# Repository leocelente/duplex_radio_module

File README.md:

# Duplex SX126x Radio Module

Board with 2 radios, STM32 and USB or CAN

## Schematic

## Layout

## Notes
The STM32F103 can't it isn't possible to use both CAN and USB 
([Source](https://community.st.com/s/article/FAQ-Concurrent-use-of-USB-and-CAN-with-STM32F103))

The intended use is to switch the interface based on the state of the SEL pin during startup process. 

## Manufacture and Assembly
The generic components and the microcontroller were chosen based on JLCPCB's Basic Parts library. That includes only the STM32, CAN transceiver, LEDs, resistors, capacitors and crystals. All connectors and the main radio modules are not included. 

|                   |           |
|-------------------|-----------|
| PCB Manufacture   | $7.00     |
| PCB Assembly      | $27.62    |
| Shipping          | $10.17    |
| Total             | $44.79    |

For 5 boards. 

Since the conversion rate of USD to BRL is around R$5,00 the cost would be R$45,00 per board. Take note that the radio module costs around R$20 on aliexpress without shipping.

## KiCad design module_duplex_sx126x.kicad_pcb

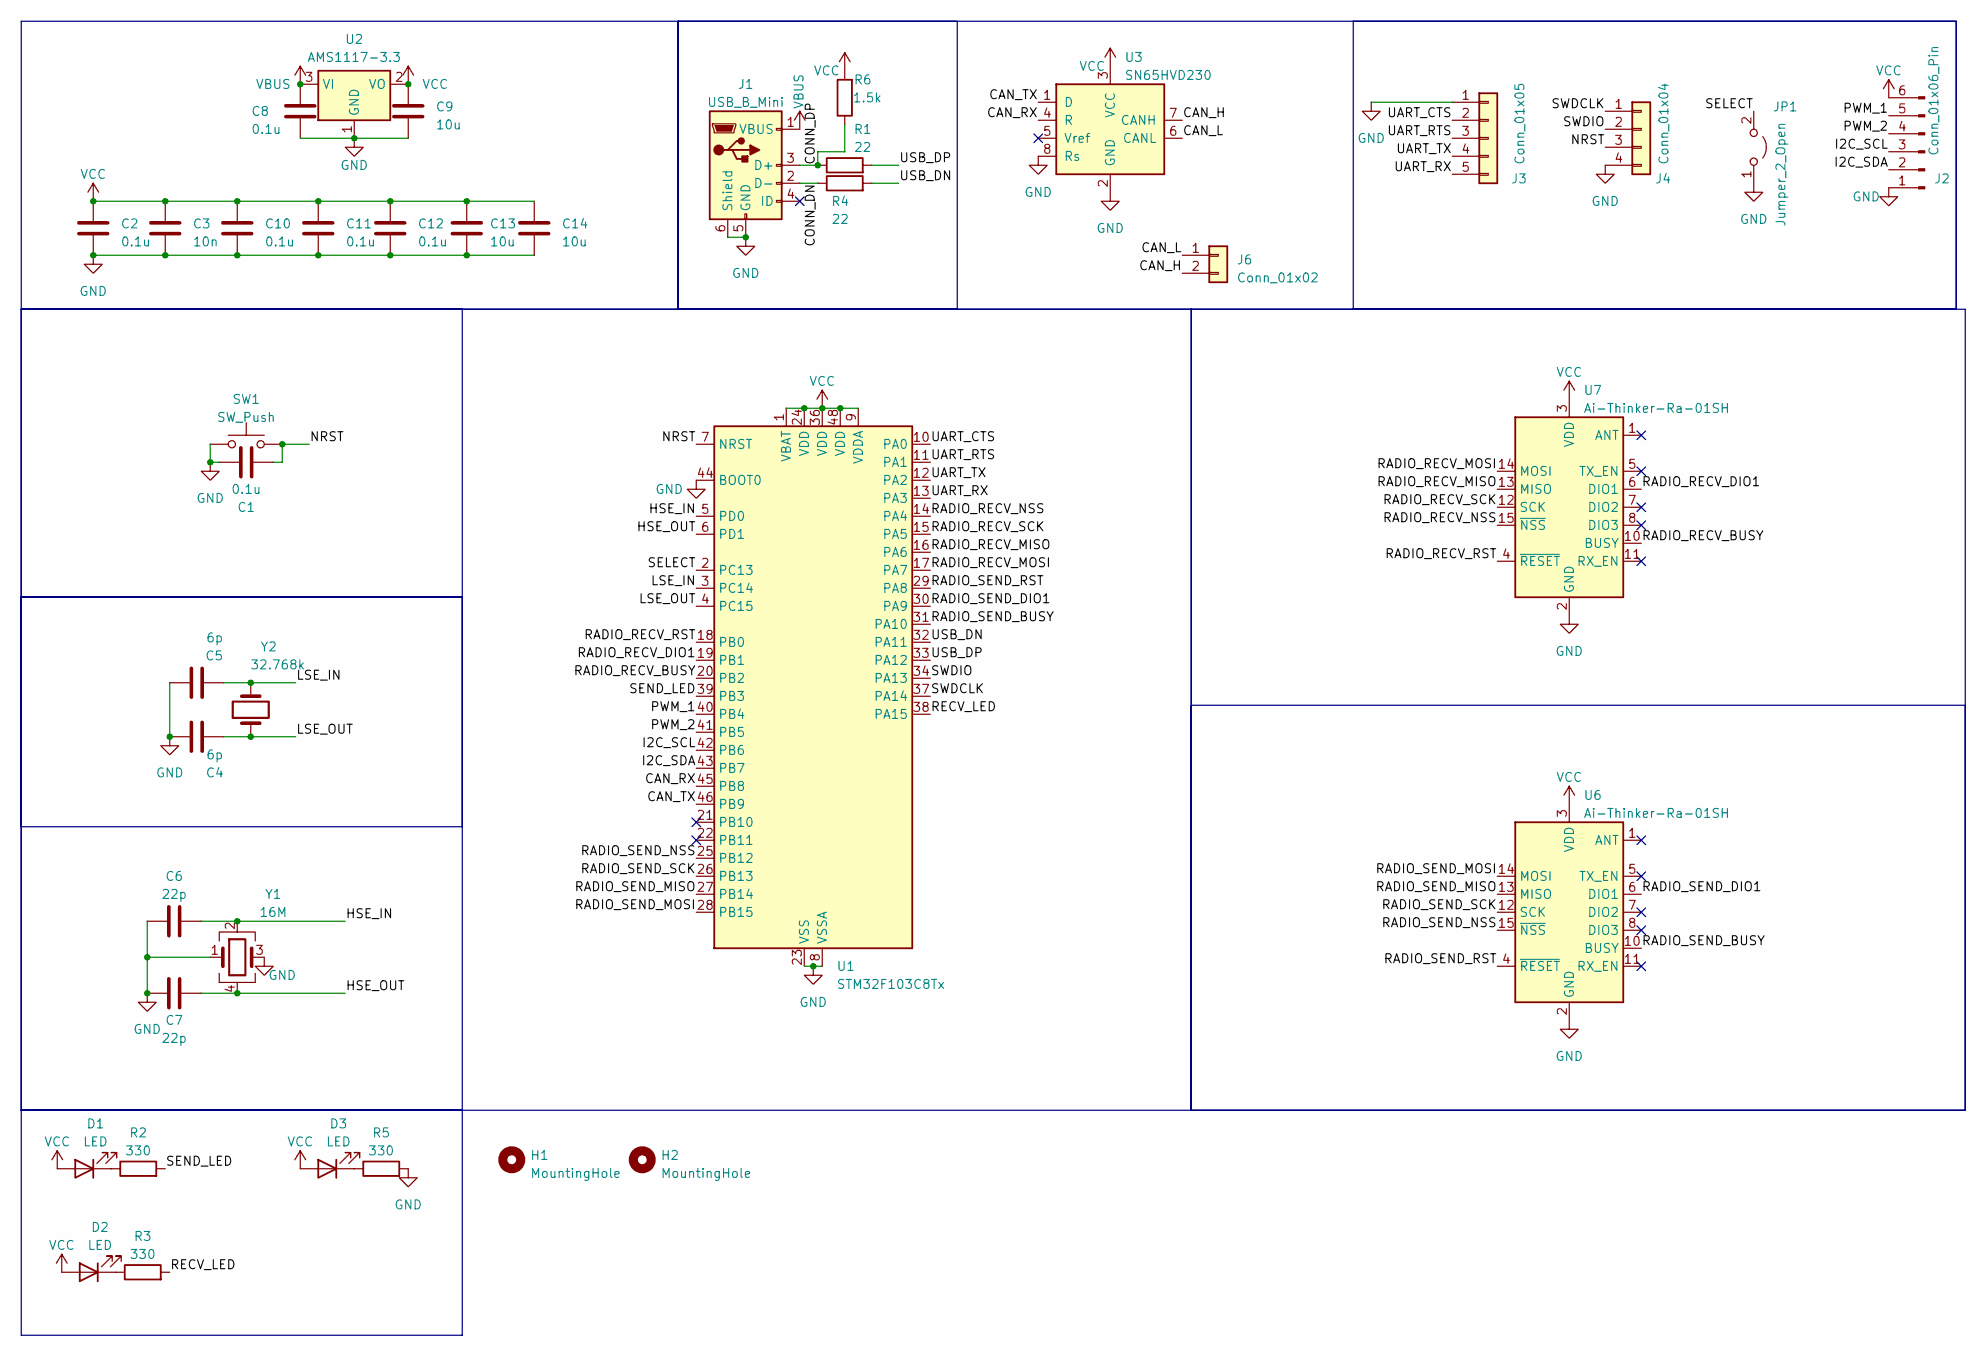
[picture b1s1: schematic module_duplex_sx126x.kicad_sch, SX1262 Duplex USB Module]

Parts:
C1, C2, C8, C10, C11, C12: 0.1u; C_0603_1608Metric; LCSC C14663
C3: 10n; C_0603_1608Metric; LCSC C57112
C4, C5: 6p; C_0603_1608Metric; LCSC C37474
C6, C7: 22p; C_0603_1608Metric; LCSC C1653
C9, C13, C14: 10u; C_0805_2012Metric; LCSC C19702
D1: LED; LED_0603_1608Metric; LCSC C72043
D2: LED; LED_0603_1608Metric; LCSC C72041
D3: LED; LED_0603_1608Metric; LCSC C2286
H1, H2: MountingHole; MountingHole_3.2mm_M3_Pad
J1: USB_B_Mini; USB_Mini-B_Lumberg_2486_01_Horizontal
J2: Conn_01x06_Pin; PinHeader_1x06_P2.54mm_Vertical
J3: Conn_01x05; JST_PH_S5B-PH-K_1x05_P2.00mm_Horizontal
J4: Conn_01x04; JST_PH_B4B-PH-K_1x04_P2.00mm_Vertical
J6: Conn_01x02; JST_PH_S2B-PH-K_1x02_P2.00mm_Horizontal
JP1: Jumper_2_Open; PinHeader_1x02_P2.54mm_Vertical
R1, R4: 22; R_0603_1608Metric; LCSC C23345
R2, R3, R5: 330; R_0603_1608Metric; LCSC C23138
R6: 1.5k; R_0603_1608Metric; LCSC C22843
SW1: SW_Push; SW_SPST_TL3342; LCSC C318884
U1: STM32F103C8Tx; LQFP-48_7x7mm_P0.5mm; LCSC C8734
U2: AMS1117-3.3; SOT-223-3_TabPin2; LCSC C6186
U3: SN65HVD230; SOIC-8_3.9x4.9mm_P1.27mm; LCSC C12084
U6, U7: Ai-Thinker-Ra-01SH; Ai-Thinker-Ra-01-LoRa
Y1: 16M; Crystal_SMD_3225-4Pin_3.2x2.5mm; LCSC C13738
Y2: 32.768k; Crystal_SMD_3215-2Pin_3.2x1.5mm; LCSC C32346

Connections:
/CAN_H: J6.2, U3.7 (CANH)
/CAN_L: J6.1, U3.6 (CANL)
/CAN_RX: U1.45 (PB8), U3.4 (R)
/CAN_TX: U1.46 (PB9), U3.1 (D)
/CONN_DN: J1.2 (D-), R4.1
/CONN_DP: J1.3 (D+), R1.1, R6.1
/HSE_IN: C6.2, U1.5 (PD0), Y1.2
/HSE_OUT: C7.2, U1.6 (PD1), Y1.4
/I2C_SCL: J2.3, U1.42 (PB6)
/I2C_SDA: J2.2, U1.43 (PB7)
/LSE_IN: C5.2, U1.3 (PC14), Y2.2
/LSE_OUT: C4.2, U1.4 (PC15), Y2.1
/NRST: C1.2, J4.3, SW1.2, U1.7 (NRST)
/PWM_1: J2.5, U1.40 (PB4)
/PWM_2: J2.4, U1.41 (PB5)
/RADIO_RECV_BUSY: U1.20 (PB2), U7.10 (BUSY)
/RADIO_RECV_DIO1: U1.19 (PB1), U7.6 (DIO1)
/RADIO_RECV_MISO: U1.16 (PA6), U7.13 (MISO)
/RADIO_RECV_MOSI: U1.17 (PA7), U7.14 (MOSI)
/RADIO_RECV_NSS: U1.14 (PA4), U7.15 (~NSS)
/RADIO_RECV_RST: U1.18 (PB0), U7.4 (~RESET)
/RADIO_RECV_SCK: U1.15 (PA5), U7.12 (SCK)
/RADIO_SEND_BUSY: U1.31 (PA10), U6.10 (BUSY)
/RADIO_SEND_DIO1: U1.30 (PA9), U6.6 (DIO1)
/RADIO_SEND_MISO: U1.27 (PB14), U6.13 (MISO)
/RADIO_SEND_MOSI: U1.28 (PB15), U6.14 (MOSI)
/RADIO_SEND_NSS: U1.25 (PB12), U6.15 (~NSS)
/RADIO_SEND_RST: U1.29 (PA8), U6.4 (~RESET)
/RADIO_SEND_SCK: U1.26 (PB13), U6.12 (SCK)
/RECV_LED: R3.2, U1.38 (PA15)
/SELECT: JP1.2 (B), U1.2 (PC13)
/SEND_LED: R2.2, U1.39 (PB3)
/SWDCLK: J4.1, U1.37 (PA14)
/SWDIO: J4.2, U1.34 (PA13)
/UART_CTS: J3.2, U1.10 (PA0)
/UART_RTS: J3.3, U1.11 (PA1)
/UART_RX: J3.5, U1.13 (PA3)
/UART_TX: J3.4, U1.12 (PA2)
/USB_DN: R4.2, U1.32 (PA11)
/USB_DP: R1.2, U1.33 (PA12)
GND: C1.1, C2.2, C3.2, C4.1, C5.1, C6.1, C7.1, C8.2, C9.2, C10.2, C11.2, C12.2, C13.2, C14.2, J1.5 (GND), J1.6 (Shield), J2.1, J3.1, J4.4, JP1.1 (A), R5.2, SW1.1, U1.8 (VSSA), U1.23 (VSS), U1.35 (VSS), U1.44 (BOOT0), U1.47 (VSS), U2.1 (GND), U3.2 (GND), U3.8 (Rs), U6.2 (GND), U6.9 (GND), U6.16 (GND), U7.2 (GND), U7.9 (GND), U7.16 (GND), Y1.1, Y1.3
unnamed: D1.1 (K), R2.1
unnamed: D2.1 (K), R3.1
unnamed: D3.1 (K), R5.1
VBUS: C8.1, J1.1 (VBUS), U2.3 (VI)
VCC: C2.1, C3.1, C9.1, C10.1, C11.1, C12.1, C13.1, C14.1, D1.2 (A), D2.2 (A), D3.2 (A), J2.6, R6.2, U1.1 (VBAT), U1.9 (VDDA), U1.24 (VDD), U1.36 (VDD), U1.48 (VDD), U2.2 (VO), U3.3 (VCC), U6.3 (VDD), U7.3 (VDD)

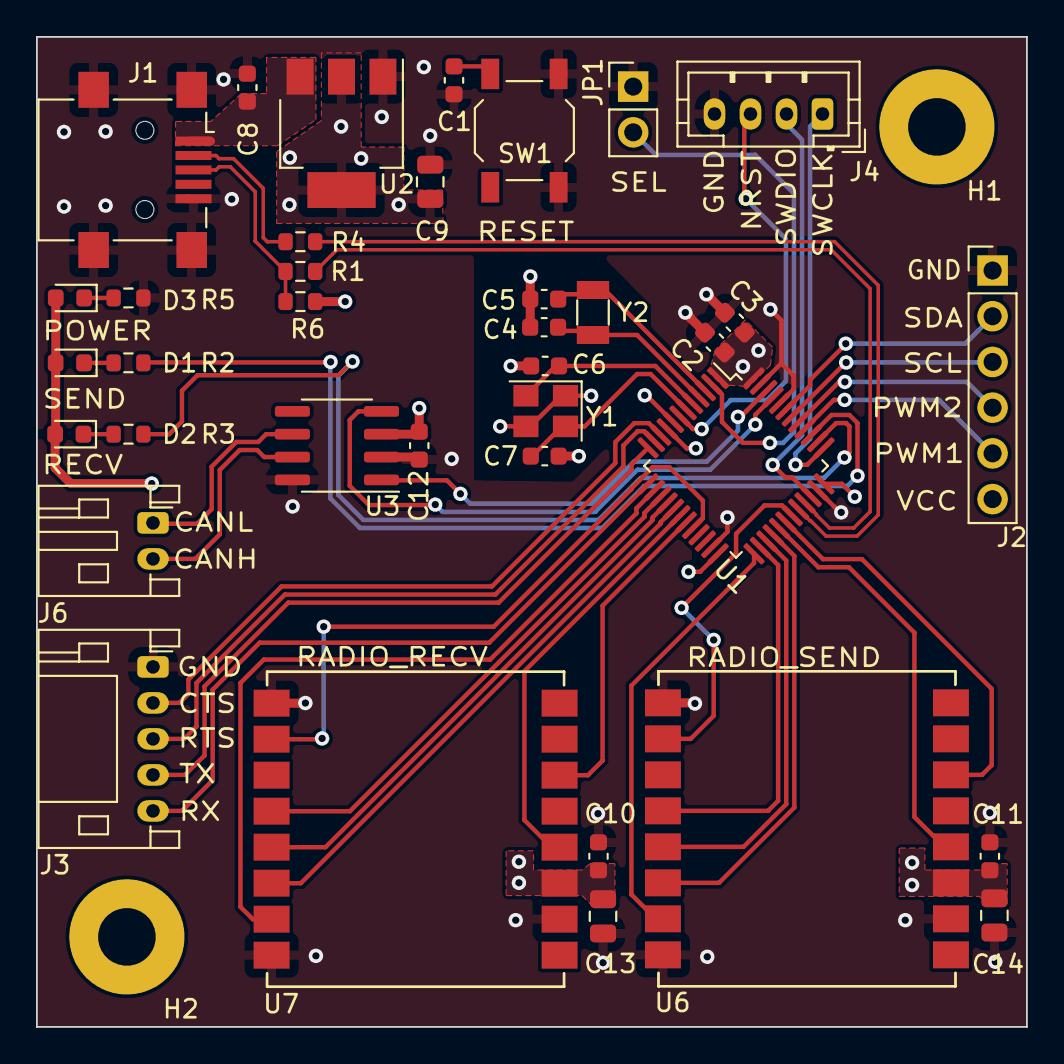
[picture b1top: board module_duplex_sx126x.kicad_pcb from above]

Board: 4 copper layers, 55.0 x 55.0 mm, 39 parts (0 on the bottom side), 46 nets.

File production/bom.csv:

Designator,Footprint,Quantity,Value,LCSC Part #
"C1, C10, C11, C12, C2, C8",0603,6,0.1u,C14663
"C13, C14, C9",0805,3,10u,C19702
C3,0603,1,10n,C57112
"C4, C5",0603,2,6p,C37474
"C6, C7",0603,2,22p,C1653
"D1, D2, D3",0603,3,LED,C72043
"R1, R4",0603,2,22,C23345
"R2, R3, R5",0603,3,330,C23138
R6,0603,1,1.5k,C22843
SW1,SW_SPST_TL3342,1,SW_Push,C318884
U1,LQFP-48_7x7mm_P0.5mm,1,STM32F103C8Tx,C8734
U2,SOT-223-3_TabPin2,1,AMS1117-3.3,C6186
U3,SOIC-8_3.9x4.9mm_P1.27mm,1,SN65HVD230,C12084
Y1,Crystal_SMD_3225-4Pin_3.2x2.5mm,1,16M,C13738
Y2,Crystal_SMD_3215-2Pin_3.2x1.5mm,1,32.768k,C32346

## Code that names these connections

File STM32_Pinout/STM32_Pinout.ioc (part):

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Mcu.Name=STM32F103C(8-B)Tx
Mcu.Package=LQFP48
Mcu.UserName=STM32F103C8Tx
PA0-WKUP.Mode=CTS_RTS
PA0-WKUP.Signal=USART2_CTS
PA1.Mode=CTS_RTS
PA1.Signal=USART2_RTS
PA10.GPIOParameters=GPIO_Label
PA10.GPIO_Label=SPI2_INT1
PA10.Signal=GPXTI10
PA11.Mode=Device
PA11.Signal=USB_DM
PA12.Mode=Device
PA12.Signal=USB_DP
PA13.Mode=Serial_Wire
PA13.Signal=SYS_JTMS-SWDIO
PA14.Mode=Serial_Wire
PA14.Signal=SYS_JTCK-SWCLK
PA15.GPIOParameters=GPIO_Label
PA15.GPIO_Label=LED_RECV
PA15.Signal=GPIO_Output
PA2.Mode=Asynchronous
PA2.Signal=USART2_TX
PA3.Mode=Asynchronous
PA3.Signal=USART2_RX
PA4.Mode=NSS_Signal_Hard_Output
PA4.Signal=SPI1_NSS
PA5.Mode=Full_Duplex_Master
PA5.Signal=SPI1_SCK
PA6.Mode=Full_Duplex_Master
PA6.Signal=SPI1_MISO
PA7.Mode=Full_Duplex_Master
PA7.Signal=SPI1_MOSI
PA8.GPIOParameters=GPIO_Label
PA8.GPIO_Label=SPI2_RST
PA8.Signal=GPIO_Output
PA9.GPIOParameters=GPIO_Label
PA9.GPIO_Label=SPI2_TXEN
PA9.Signal=GPXTI9
PB0.GPIOParameters=GPIO_Label
PB0.GPIO_Label=SPI1_RST
PB0.Signal=GPIO_Output
PB1.GPIOParameters=GPIO_Label
PB1.GPIO_Label=SPI1_TXEN
PB1.Signal=GPXTI1
PB12.Mode=NSS_Signal_Hard_Output
PB12.Signal=SPI2_NSS
PB13.Mode=Full_Duplex_Master
PB13.Signal=SPI2_SCK
PB14.Mode=Full_Duplex_Master
PB14.Signal=SPI2_MISO
PB15.Mode=Full_Duplex_Master
PB15.Signal=SPI2_MOSI
PB2.GPIOParameters=GPIO_Label
PB2.GPIO_Label=SPI1_INT1
PB2.Signal=GPXTI2
PB3.GPIOParameters=GPIO_Label
PB3.GPIO_Label=LED_SEND
PB3.Signal=GPIO_Output
PB4.GPIOParameters=GPIO_Label
PB4.GPIO_Label=PWM1
PB4.Signal=S_TIM3_CH1
PB5.GPIOParameters=GPIO_Label
PB5.GPIO_Label=PWM2
PB5.Signal=S_TIM3_CH2
PB6.Mode=I2C
PB6.Signal=I2C1_SCL
PB7.Mode=I2C
PB7.Signal=I2C1_SDA
PB8.Mode=CAN_Activate
PB8.Signal=CAN_RX
PB9.Mode=CAN_Activate
PB9.Signal=CAN_TX
PC13-TAMPER-RTC.GPIOParameters=GPIO_PuPd,GPIO_Label
PC13-TAMPER-RTC.GPIO_Label=SELECT
PC13-TAMPER-RTC.GPIO_PuPd=GPIO_PULLUP
PC13-TAMPER-RTC.Signal=GPIO_Input
PC14-OSC32_IN.Mode=LSE-External-Oscillator
PC14-OSC32_IN.Signal=RCC_OSC32_IN
PC15-OSC32_OUT.Mode=LSE-External-Oscillator
PC15-OSC32_OUT.Signal=RCC_OSC32_OUT
PD0-OSC_IN.Mode=HSE-External-Oscillator
PD0-OSC_IN.Signal=RCC_OSC_IN
PD1-OSC_OUT.Mode=HSE-External-Oscillator
PD1-OSC_OUT.Signal=RCC_OSC_OUT
RCC.HSEDivPLL=RCC_HSE_PREDIV_DIV2
RCC.HSE_VALUE=16000000
RCC.SYSCLKFreq_VALUE=72000000
RCC.SYSCLKSource=RCC_SYSCLKSOURCE_PLLCLK
board=custom

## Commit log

2023-05-15 First Schematic and layout position
2023-05-15 Reduced expansion pins by simplifying select function with pull up/down
2023-05-15 Added USB resistors
2023-05-15 Added power indicator LED
2023-05-19 First Pass routing top copper layer
2023-05-19 Added RCC settings and USB device class
2023-05-19 First Pass of full layout
2023-05-19 Added Fabrication folder to gitignore
2023-05-20 Removed fabrication directory rule, added autosave files rule
2023-05-20 Added LCSC part numbers for production
2023-05-20 Latest generated production files (using JLC Fabrication plugin)
2023-05-20 Minor tweaks to vias
2023-05-20 Thought I had saved
2023-05-20 Changed connector to jumper; Added USB DM pullup
2023-05-20 removed in-pad vias
2023-05-20 Production Update
2023-05-20 Moved pull up to correct USB_DP
2023-05-27 Corrected DIO1 BUSY pin in radio module
2023-05-27 removed backups
2023-05-28 Added silkscreen diagram and symbols
2023-05-29 Updated Production and added README
2023-05-29 Better layout screenshot
2023-05-30 Improved layout from Pudim's feedback
2023-05-30 updated images
